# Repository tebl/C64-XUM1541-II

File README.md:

# C64 XUM1541-II
About a year ago I had a look at my collection of Commodore 64 floppies and decided that it was time, enough time had passed that even I needed to look into backing them up - hoping simply doesn't cut it in the end. I had a look at the available options, then instead of just choosing to buy something like the ZoomFloppy I wanted to build it myself. With the resources available to me [online](https://myoldcomputer.nl/commodore-64/xum1541-promicro/), all of the heavy lifting was already done. The work of transferring the designs to PCB using KiCAD resulted in the previous version, creatively called [C64 XUM1541](https://github.com/tebl/C64-XUM1541). Now that a year has gone by, mostly isolated like most of the world I wanted to make a new revision with few tweaks and so I made the  *C64 XUM1541-II*.

What had somewhat annoyed me that the [C64 XUM1541](https://github.com/tebl/C64-XUM1541) was its apparant limition when it came to running anything past version 0.7 of the [OpenCBM](https://github.com/OpenCBM/OpenCBM/tree/master/xum1541) firmware, so I finally got around to actually reading the documentation that came with it. I don't know the exact point in time the designs parted ways, but thinking practically - I instead just focused on making a version of it that would work. Mostly by adding the components required for the 7406-version of the reference design included with *OpenCBM*.

Not quite substantial enough to warrant documenting them as separate projects, I've also taken a look at implementing some of the simpler upgrades for the Commodore 1541-II as they are the type of drives I have available. Read through the included documentation before attempting to perform any of the upgrades as well as ensuring that they actually fit into the drive you have.

# 1> Modules
The following modules are available as part of this project. The additional modules are strictly not necessary as you can simply use the *C64 XUM1541-II* by itself with a drive, the parallel interface will cut the time needed to backup a single disk in half. The remaining modules mainly just affect your experience when using the drive with your physical Commodore 64, but note that most of them have been designed for use with a Commodore 1541-II disk drive.  The SpeedDOS user port adapter has been included for completeness, but before getting excited about the possiblities you should be aware that the speed gains will probably be less than what you'd obtain by simply installing [JiffyDOS](http://store.go4retro.com/categories/Commodore/Firmware/JiffyDOS/) in your [disk drive](http://store.go4retro.com/jiffydos-1541-dos-rom-overlay-image/) as well as  the [computer](http://store.go4retro.com/jiffydos-64-kernal-rom-overlay-image/) itself.

The following table lists all of the modules, click the name to get a more detailed description as well as other information for that specific module. The second and third column has been added to show which module can be used with each other, the 'XUM1541' giving a recommendation when performing backups on a modern computer. The  third column provides a recommendation when you want to use the modified drive with your physical Commodore 64.

| Module                  | C64 XUM1541-II | Physical C64 | Order  | Description |
| ----------------------- | -------------- | ------------ | ------ | ----------- |
| [C64 XUM1541-II](https://github.com/tebl/C64-XUM1541-II/tree/main/C64%20XUM1541-II) | required       | N/A     | [PCBWay](https://www.pcbway.com/project/shareproject/C64_XUM1541_II.html) | C64 XUM1541-II module for backing disks up to modern computer.
| [C64 XUM1541-II Faceplate](https://github.com/tebl/C64-XUM1541-II/tree/main/faceplates) | optional       | N/A     | [PCBWay FA1](https://www.pcbway.com/project/shareproject/C64_XUM1541_II__Faceplate_FA1_.html) | Optional faceplates suitable for installing on top of [C64 XUM1541-II](https://github.com/tebl/C64-XUM1541-II/tree/main/C64%20XUM1541-II), hiding away most of the electronics in a way that would mimic a case with a minimal amount of work.
| C64 1541-II VIA Adapter | recommended    | optional     | PCBWay | Adds a parallel interface to your Commodore 1541-II disk drive, can be used with both [C64 XUM1541-II](https://github.com/tebl/C64-XUM1541-II/tree/main/C64%20XUM1541-II) as well as physical computer with a suitable ROM upgrade.
| [C64 1541-II ROM Adapter](https://github.com/tebl/C64-XUM1541-II/tree/main/C64%201541-II%20ROM%20Adapter) | optional       | recommended  | PCBWay | Adds a switch to select between ROM images suitable for Commodore 1541-II disk drive with only a single 16KB ROM chip.
| C64 SpeedDOS Adapter    | N/A            | optional     | PCBWay | User port adapter for connecting a 1541-II disk drive with a parallel cable up to your Commodore 64, requires matching firmware on the drive as well as the computer.
| [C64 Kernal Switcher](https://github.com/tebl/C64-Kernal-Switcher) | N/A          | recommended  | [PCBWay](https://www.pcbway.com/project/shareproject/Commodore_64_Quad_Kernal_Switcher.html?inviteid=88707) | Using a custom kernal with optimizations for either serial or parallel interfaces is recommended. This board was designed for use with C64 "Longboards".

# 2> Documentation
Building an XUM1541 from scratch and getting the software ready to transfer your own physical disks, is a rather involving process. It is an afternoons worth of a project, but by following the documentation it shouldn't be a difficult task for anyone equipped with a brain for slight engineering. As the project really is just a collection of various modules that you may or may not need, I've separated the information so that the relevant documentation is included as a separate README for each of the [modules](#1-modules) - click the module name for BOM, build instructions and so forth.

When you're ready to start installing software, by first installing the firmware onto the *Arduino Pro Micro* and then installing OpenCBM, there's a separate document covering these details:
- [Firmware installation](https://github.com/tebl/C64-XUM1541-II/blob/main/documentation/firmware.md)

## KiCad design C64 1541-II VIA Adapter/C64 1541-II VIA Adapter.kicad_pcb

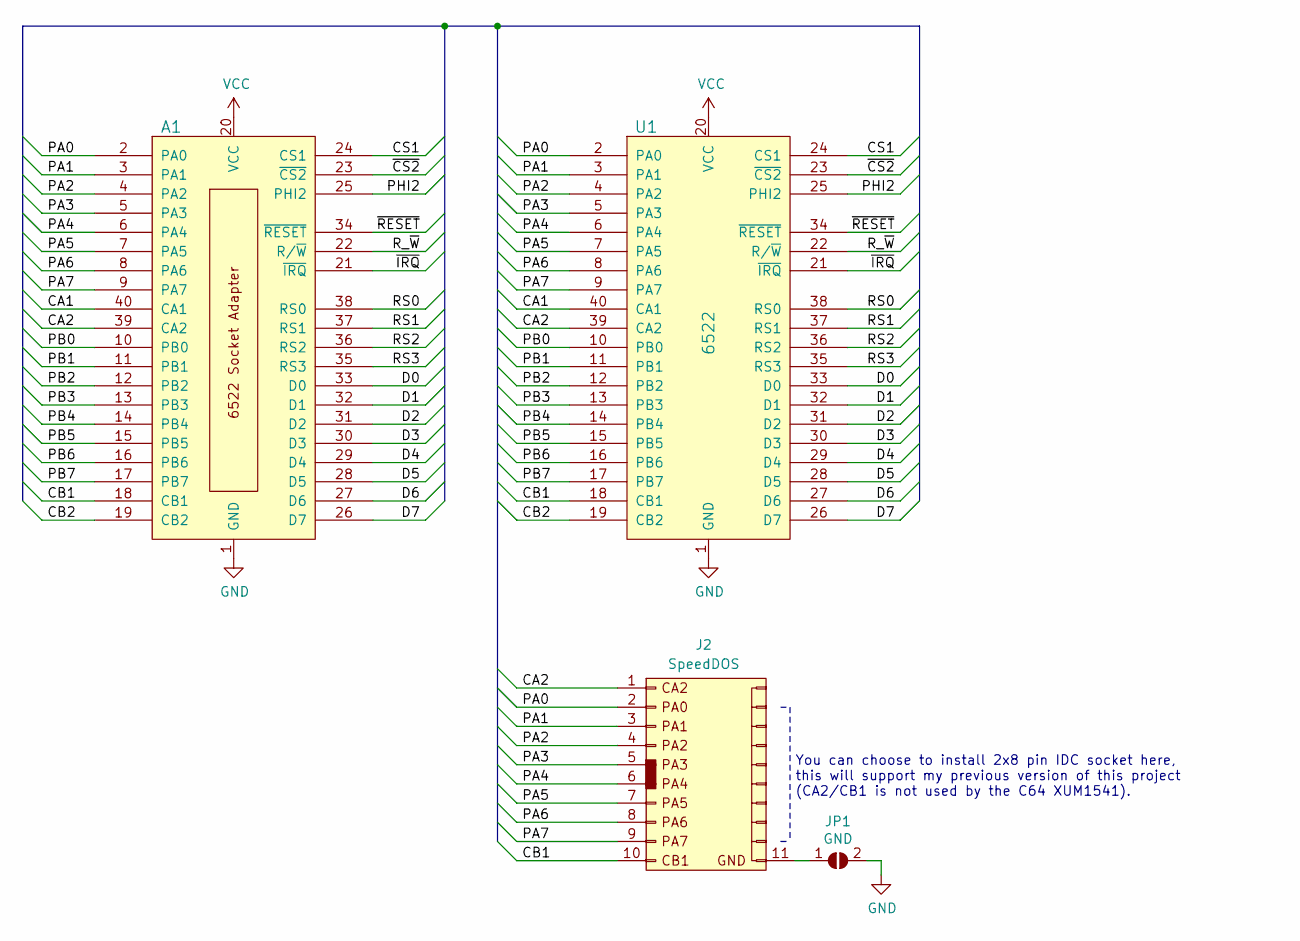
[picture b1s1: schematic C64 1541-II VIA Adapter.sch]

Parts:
A1: 6522_Adapter; DIP-40_W15.24mm_Socket
J2: SpeedDOS; SpeedDOS_IDC
JP1: GND; bridge_r
U1: 6522; DIP-40_W15.24mm_Socket

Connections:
/CA1: A1.40 (CA1), U1.40 (CA1)
/CA2: A1.39 (CA2), J2.1, U1.39 (CA2)
/CB1: A1.18 (CB1), J2.10, U1.18 (CB1)
/CB2: A1.19 (CB2), U1.19 (CB2)
/CS1: A1.24 (CS1), U1.24 (CS1)
/D0: A1.33 (D0), U1.33 (D0)
/D1: A1.32 (D1), U1.32 (D1)
/D2: A1.31 (D2), U1.31 (D2)
/D3: A1.30 (D3), U1.30 (D3)
/D4: A1.29 (D4), U1.29 (D4)
/D5: A1.28 (D5), U1.28 (D5)
/D6: A1.27 (D6), U1.27 (D6)
/D7: A1.26 (D7), U1.26 (D7)
/PA0: A1.2 (PA0), J2.2, U1.2 (PA0)
/PA1: A1.3 (PA1), J2.3, U1.3 (PA1)
/PA2: A1.4 (PA2), J2.4, U1.4 (PA2)
/PA3: A1.5 (PA3), J2.5, U1.5 (PA3)
/PA4: A1.6 (PA4), J2.6, U1.6 (PA4)
/PA5: A1.7 (PA5), J2.7 (Pin_5), U1.7 (PA5)
/PA6: A1.8 (PA6), J2.8, U1.8 (PA6)
/PA7: A1.9 (PA7), J2.9, U1.9 (PA7)
/PB0: A1.10 (PB0), U1.10 (PB0)
/PB1: A1.11 (PB1), U1.11 (PB1)
/PB2: A1.12 (PB2), U1.12 (PB2)
/PB3: A1.13 (PB3), U1.13 (PB3)
/PB4: A1.14 (PB4), U1.14 (PB4)
/PB5: A1.15 (PB5), U1.15 (PB5)
/PB6: A1.16 (PB6), U1.16 (PB6)
/PB7: A1.17 (PB7), U1.17 (PB7)
/PHI2: A1.25 (PHI2), U1.25 (PHI2)
/RS0: A1.38 (RS0), U1.38 (RS0)
/RS1: A1.37 (RS1), U1.37 (RS1)
/RS2: A1.36 (RS2), U1.36 (RS2)
/RS3: A1.35 (RS3), U1.35 (RS3)
/R_~W: A1.22 (R/~W), U1.22 (R/~W)
/~CS2: A1.23 (~CS2), U1.23 (~CS2)
/~IRQ: A1.21 (~IRQ), U1.21 (~IRQ)
/~RESET: A1.34 (~RESET), U1.34 (~RESET)
GND: A1.1 (GND), JP1.2 (B), U1.1 (GND)
unnamed: J2.11, JP1.1 (A)
VCC: A1.20 (VCC), U1.20 (VCC)

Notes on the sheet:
You can choose to install 2x8 pin IDC socket here, this will support my previous version of this project (CA2/CB1 is not used by the C64 XUM1541).

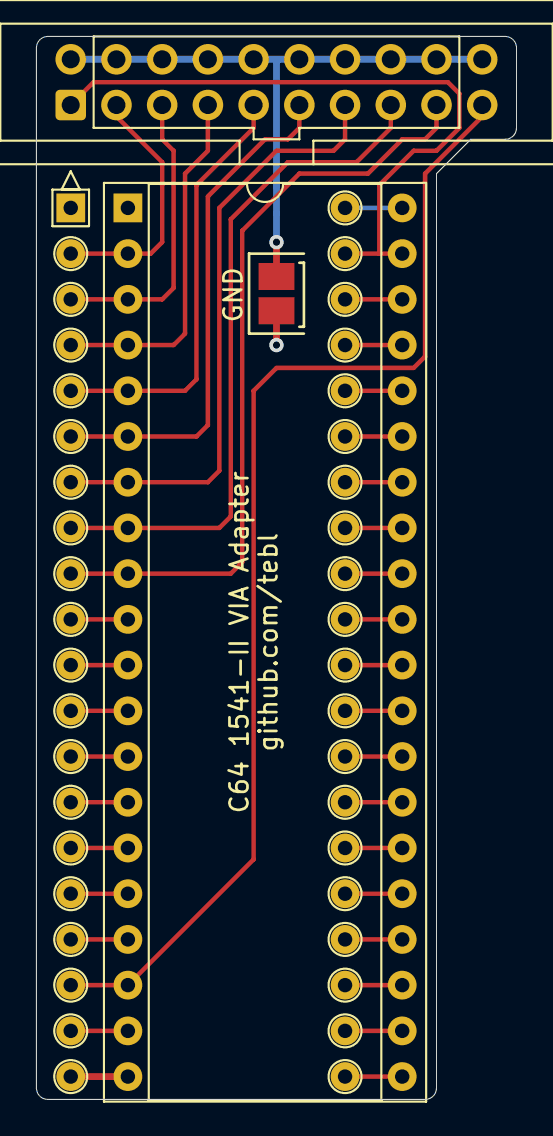
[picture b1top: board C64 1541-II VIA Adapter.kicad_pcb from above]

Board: 2 copper layers, 26.7 x 59.1 mm, 4 parts (0 on the bottom side), 41 nets.

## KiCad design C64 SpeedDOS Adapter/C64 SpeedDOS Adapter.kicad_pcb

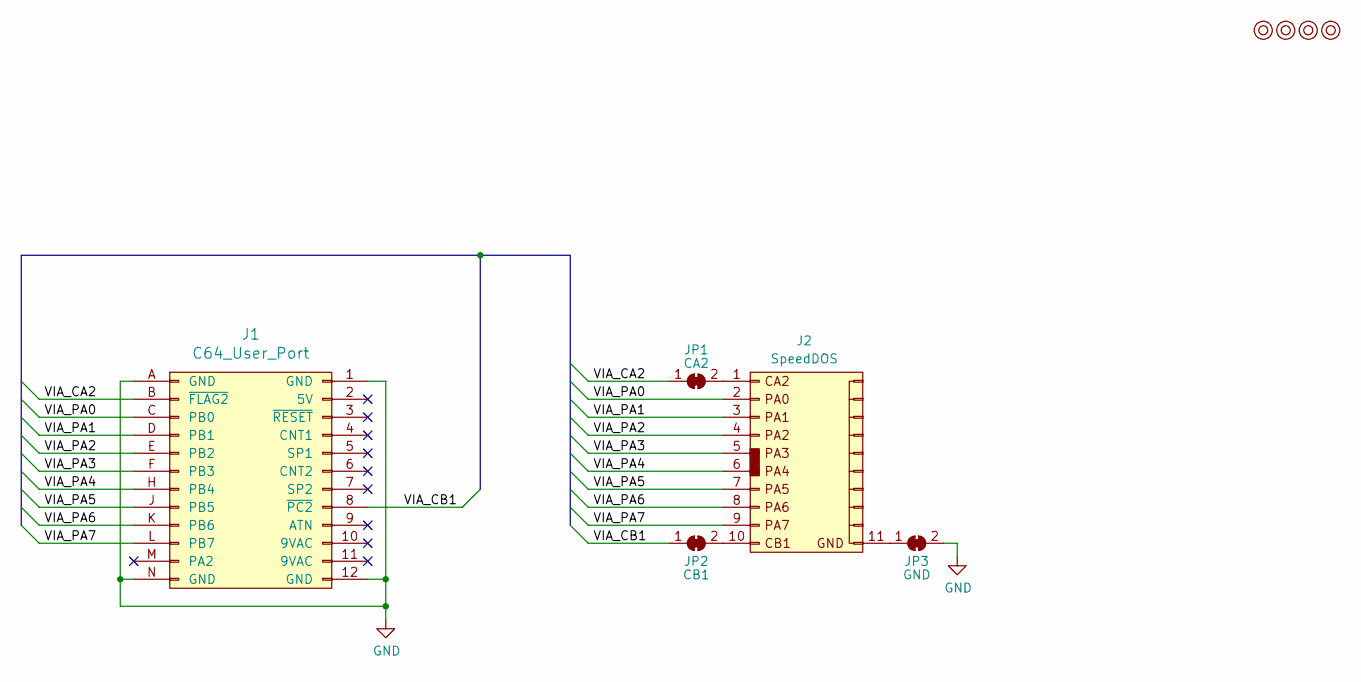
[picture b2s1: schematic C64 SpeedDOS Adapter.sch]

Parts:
J1: C64_User_Port; C64_User-Port
J2: SpeedDOS; SpeedDOS_IDC
JP1: CA2; bridge
JP2: CB1; bridge_r
JP3: GND; bridge
M1, M2, M3, M4: Mounting; M3_pin

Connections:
/VIA_CA2: J1.B (~FLAG2), JP1.1 (A)
/VIA_CB1: J1.8 (~PC2), JP2.1 (A)
/VIA_PA0: J1.C (PB0), J2.2
/VIA_PA1: J1.D (PB1), J2.3
/VIA_PA2: J1.E (PB2), J2.4
/VIA_PA3: J1.F (PB3), J2.5
/VIA_PA4: J1.H (PB4), J2.6
/VIA_PA5: J1.J (PB5), J2.7 (Pin_5)
/VIA_PA6: J1.K (PB6), J2.8
/VIA_PA7: J1.L (PB7), J2.9
GND: J1.1 (GND), J1.12 (GND), J1.A (GND), J1.N (GND), JP3.2 (B)
unnamed: J2.1, JP1.2 (B)
unnamed: J2.10, JP2.2 (B)
unnamed: J2.11, JP3.1 (A)

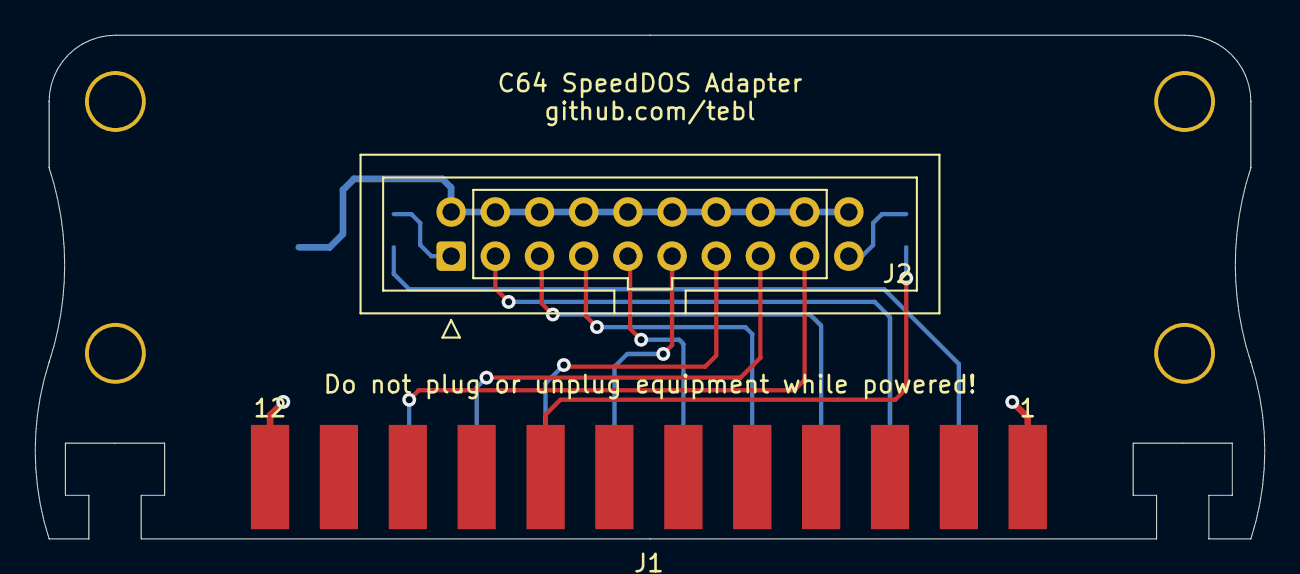
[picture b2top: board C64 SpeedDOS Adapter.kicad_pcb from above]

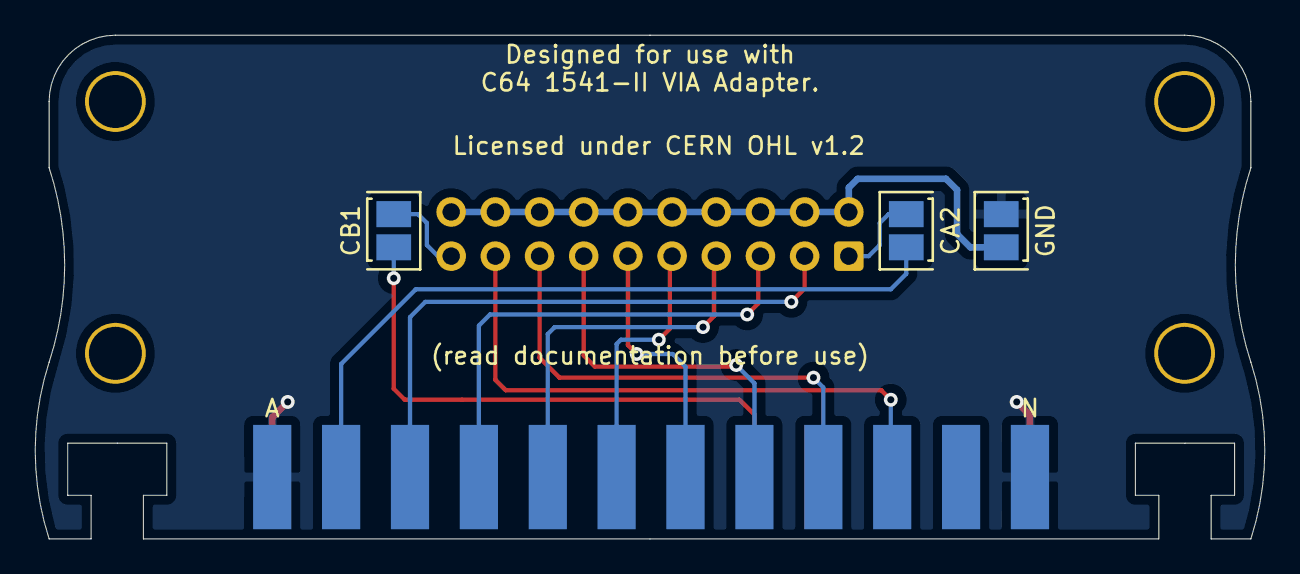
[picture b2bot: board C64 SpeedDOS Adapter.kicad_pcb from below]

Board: 2 copper layers, 70.7 x 29.0 mm, 9 parts (3 on the bottom side), 14 nets.

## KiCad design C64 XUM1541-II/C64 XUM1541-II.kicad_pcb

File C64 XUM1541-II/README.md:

# C64 XUM1541-II
If you came to this github-repository looking for the implementation of an XUM1541, then you've come to the correct place and this folder contains all of the files needed to build one for yourself. The necessary details first of course, I didn't design the original XUM1541 - the earlier heavy lifting was already done and detailed in an  article [online](https://myoldcomputer.nl/commodore-64/xum1541-promicro/). My contribution was reading it, then adapting it for easier use by designing a PCB as part of a personal project available at [C64 XUM1541](https://github.com/tebl/C64-XUM1541).

This however is an updated version from that design, mainly by integrating the 7406 inverter as described in the [OpenCBM](https://github.com/zyonee/opencbm/tree/master/xum1541) documentation. In theory this should allow the device some more durability when used together with multiple devices connected to the IEC-bus, but while I haven't had any issue with the original device - the main objective was to modify it for use with the later versions of the OpenCBM firmware (0.8). A secondary objective was to make it a more visually pleasing device from the original, which is pretty hard when dealing with a bare PCB - so I designed a separate faceplate to be installed on the top though this is a completely optional addition.

- [1> Building the C64 XUM1541-II](#1-building-the-c64-xum1541-ii)
  - [1.1> Soldering it together](#11-soldering-it-together)
  - [1.2> Assembling the unit](#12-assembling-the-unit)
  - [1.3> Testing it out](#13-testing-it-out)
- [2> Schematic](#2-schematic)
- [3> BOM](#3-bom)

# 1> Building the C64 XUM1541-II
Building the unit assumes you have at least minor experience soldering things together, recommended is at least a soldering station with adjustable temperature to get started. Commonly you'll want to start out with some 60/40 solder tin, but this'll naturally depend on availability in your area.

With the requirements when it comes to equipment sorted, now it's time to do even more shopping - head on over to the [BOM](#3-bom)-section for a somewhat specific list over components needed. Note that with sites such as ebay, AliExpress and similar sites that sell cheap chinese components, you'll need to treat these more as a suggested search term and look for something that for the most part matches the gallery pictures. I tend to use only the cheapest components available, so it should be somewhere in the top of your results.

## 1.1> Soldering it together
The construction of this unit should be straight-forward, specifically as there are only a handful of components to deal with. None of the components overlap in any way, so while there are certainly an easier route - that one would normally go from first installing the smallest components and working your way up from there. 

I suggest that you start out by studying the PCB so that you have a general overview over the components that are needed, possibly also making a mental note over the components specificly listed in the BOM as optional (component count in parenthesis). In particular, pay attention to the markings on the board for the components that need to be installed in a specific orientation (LEDs and the single IC socket).

Here we've gone ahead and installed all of the resistors, if you've bought the components as part of a kit you should note that there are two different values that you can easily pick out based on their colour bands and the number included. The IC socket have an indent on one side, this should be matched to the silkscreen on the board.

The single capacitor doesn't have a polarity so just stick it in place. The LEDs won't function when installed in the wrong orientation, ideally this should be as easy as matching the flat side to the one on the board. However there are quite a few cheaper LEDs where this isn't as easy to determine, so instead I'll just recommend that you put the shortest pin into the hole on the *flat* side. Given that you'll no doubt want a faceplate, you need to get this on the board straight - what I recommend is that you solder one of the pins, then reheat and push the component flush with the board before soldering the remaining pin.

Here we've jumped a bit ahead and finally you've found the answer to one of your original questions; why does the outline for the Arduino Pro Micro have three sets of pins on it? As you can see from the other picture added, there are a few different layouts for the Arduino Pro Micro boards - one is wider than the other! Pick the one that matches your boards before soldering pin headers onto either of the modules.

The last component that we really need to discuss is the momentary switch, mainly that it needs to be tall enough to poke through the faceplate on top. I've not found out how ebay listings measure the height of their switches, mainly because I just picked up a kit with different size switches and picked what fit. What I can tell you is that measuring just the black protruding plastic part, it needs to be around 8mm - measured from the PCB it sits around 11.5mnm above it.

Time to shut off the soldering iron. Feel the strongth welling, return to the next chapter for the exciting conclusion to this documentation. Spoiler warning: there will be a section after that one.

## 1.2> Assembling the unit
At this point we've added just about everything but the 7406, mainly just because I like dragging things out. Before doing so, I recommend spending some time to get the firmware installed onto the Arduino Pro Micro. It shouldn't matter, but it given the number of fake 7406 chips floating around it's better doing it this way. Given that installing the firmware and the accompanying OpenCBM software can be a bit more difficult than it should be, I've put together a separate [document](https://github.com/tebl/C64-XUM1541-II/blob/main/documentation/firmware.md) that should go into just about every bit of details needed to get all that set up. Return here when you're ready to move onto testing things out.

Here we've inserted the aforementioned 7406, and the device should now be ready for actual testing. Skip to the next chapter if you don't want a faceplate, because - why wouldn't you want a faceplate? They're cool.

The faceplate is just a simple PCB, the suggested way of attaching it is by using components found in cheap *M3 nylon hex* kits. It will look at its best when using an 8mm nylon hex standoff (F-F), then adding screws from both sides. If, on the other hand, you want to stay within the kit - then I suggest using the 8mm M-F standoffs, add M3 nuts on the bottom and snip off the remaining part of the nylon screw that'll poke through. Add screws on top.

## 1.3> Testing it out
When ready to test things out, we need to do some safety notifications - mainly, you can't buy any new and unused Commodore 1541 disk drives so treat them with care. They aren't plug and play like we're used to today, if you start plugging and unplugging cables while things are powered on you should probably say a prayer. Neither probably won't actually cause your vintage computer hardware to explode, but it'll happily kill your hardware in less spectacular ways. Got that? Good.

Ensure that the 1541 disk drive as well as the C64 XUM1541-II is not powered on, now connect the  IEC cable between them. Power on the disk drive, then plug the device into your modern computer. Go through the final section of my [firmware]([document](https://github.com/tebl/C64-XUM1541-II/blob/main/documentation/firmware.md)) document for some initial hints on copying your first disk, check out the software directory for a few of the batch files I personally use with the device if you just want some basic functionality without looking into all of the options (see OpenCBM documentation for that).

# 2> Schematic
The supplied KiCad files should be sufficient as both a schematic and as a  starting point for ordering PCBs (basically you could just zip the contents of the export folder and upload that on a fabrication site), the schematic is also available in [PDF-format](https://github.com/tebl/C64-XUM1541-II/tree/main/documentation/schematic) and this is what you'll need to print and work your way through this things don't work as expected after assembly.

# 3> BOM
Most parts should be easy to get a hold of from your favourite local electronic component shop, but given that I don't have access to such shops where I live so everything was based on whatever I could get cheapest from eBay/AliExpress (free shipping, but plan on waiting 3-4 weeks for delivery). 

| Reference             | Item                                                              | Count | Order  |
| --------------------- | ----------------------------------------------------------------- | ----- | ------ |
| Cartridge PCB         | Fabricate using Gerber files                                      |     1 | [PCBWay](https://www.pcbway.com/project/shareproject/C64_XUM1541_II.html)
| Faceplate PCB         | Fabricate using Gerber files                                      |    (1)| [PCBWay FA1](https://www.pcbway.com/project/shareproject/C64_XUM1541_II__Faceplate_FA1_.html)
| A1 *                  | Arduino Pro Micro                                                 |     1 |
| C1                    | 100nF ceramic capacitor (5mm pin spacing)                         |     1 |
| D1,D2                 | 5mm LED                                                           |    (2)|
| J1                    | Female S-terminal 6pin DIN PCB                                    |     1 |
| J2                    | 2x10 male IDC socket                                              |   (1) |
| R1,R4 **              | 470 ohm resistor                                                  |    (2)| 
| R2,R3,R5,R6,R7        | 100k ohm resistor                                                 |     5 | 
| SW1                   | 6x6x11mm right-angle momentary button                             |     1 |
| U1					| 7406 (DIP-14)                                                     |     1 |
| Mounting ***          | Nylon M3 hex standoffs 8mm                                        |    (4)|
| Mounting ***          | Nylon M3x6mm nylon screws                                         |    (4)|
| Mounting ***          | M3 nylon nut                                                      |    (4)|  

*) I've purchased a couple of different Arduino Pro Micro boards that had a different physical size, so take care to match up the pins to the PCB so that you solder it up to match the board you own. 

**) The value to be installed here needs to match the LEDs installed, value should be acceptable for most cheaper LEDs. If the using LEDs in any way listed as bright or are in any way clear, you'll need to calculate a suitable value in order to not blind yourself when looking at them.

***) The easiest way of ordering these is to just one of the M3 nylon standoff kits on ebay, AliExpress or any similar sites. That way you'll get more than what you need in various sizes for future projects as well.

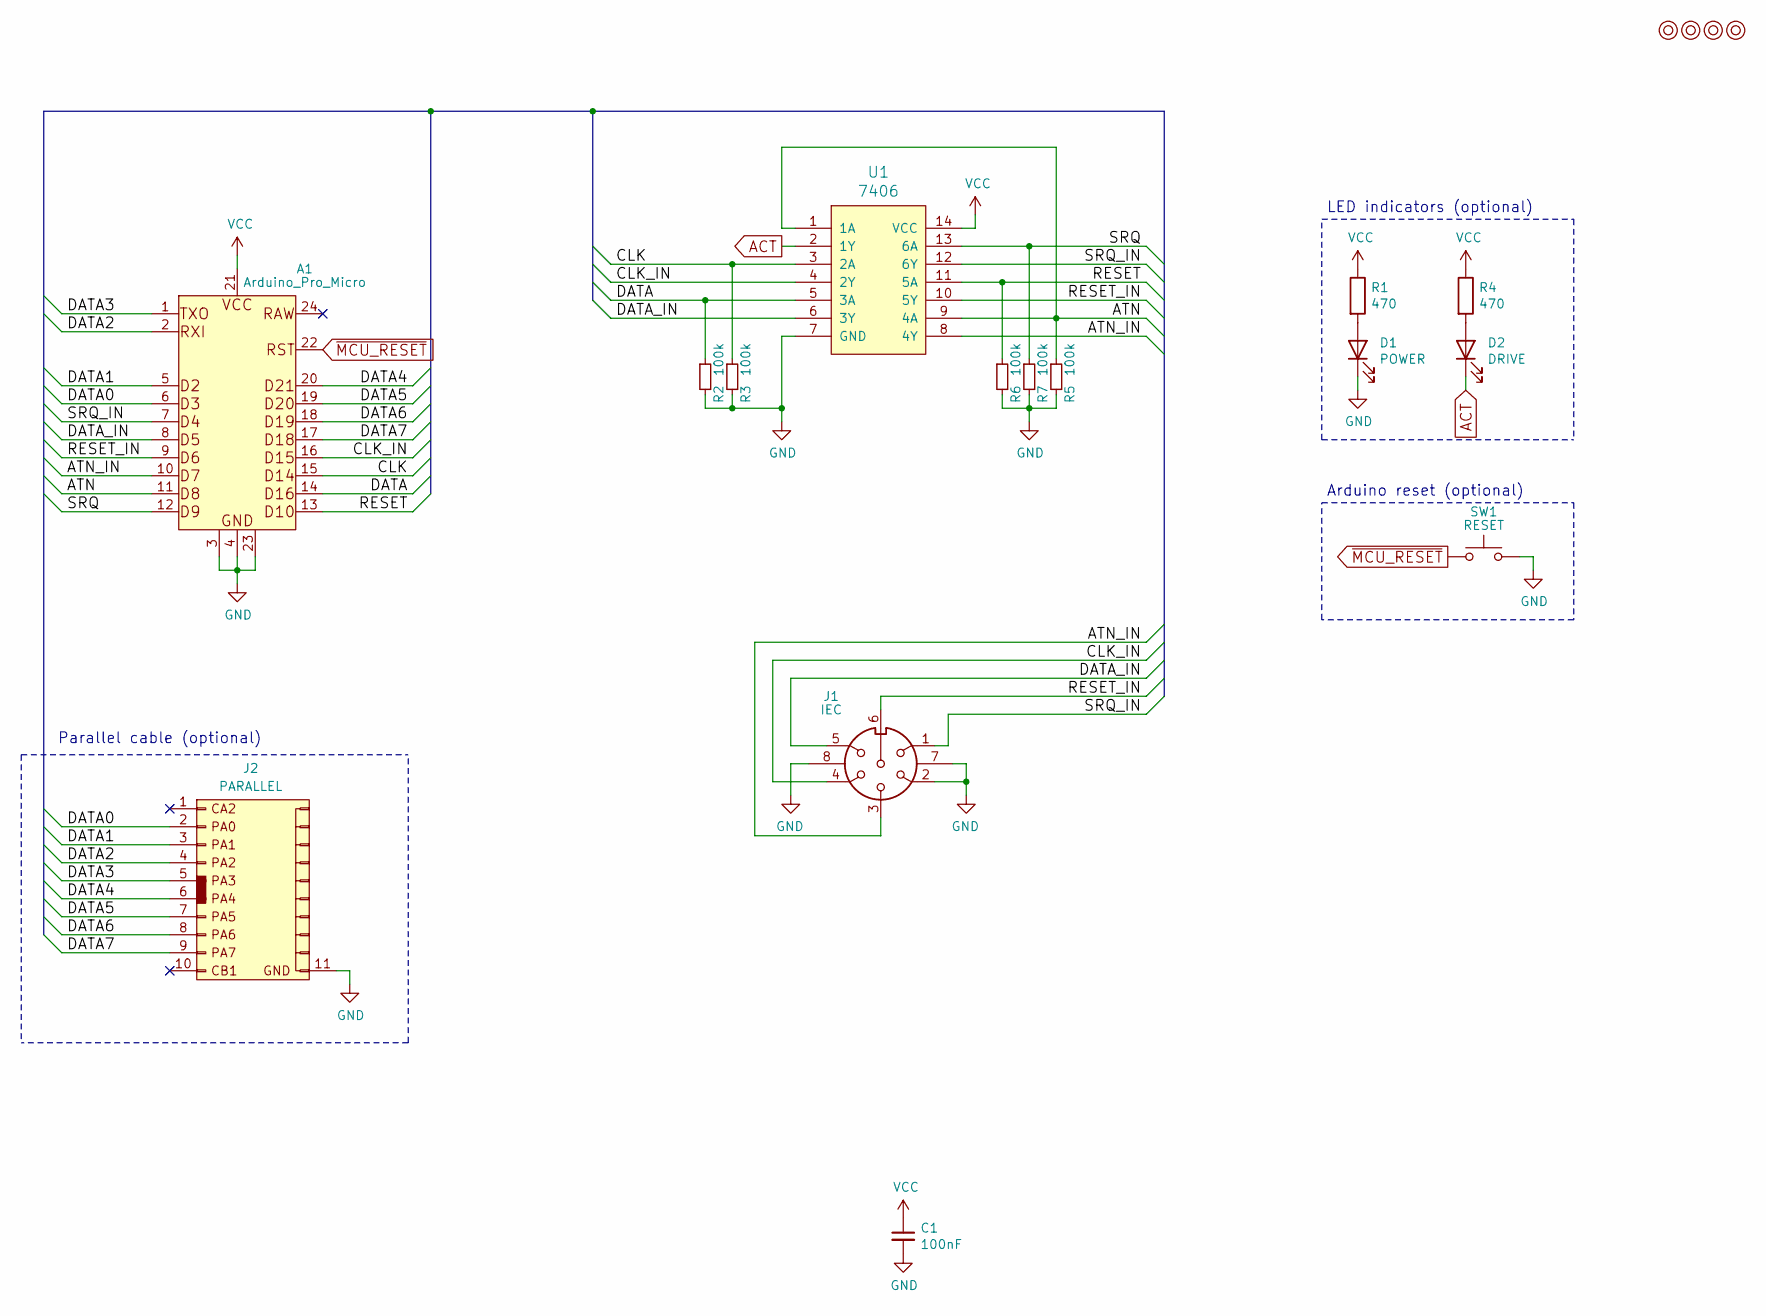
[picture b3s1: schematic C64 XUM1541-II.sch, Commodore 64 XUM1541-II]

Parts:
A1: Arduino_Pro_Micro
C1: 100nF; C_Disc_D4.7mm_W2.5mm_P5.00mm
D1: POWER; LED_D5.0mm
D2: DRIVE; LED_D5.0mm
J1: IEC; C64_IEC
J2: PARALLEL; SpeedDOS_IDC
M1, M2, M3, M4: Mounting; M3_pin
R1, R4: 470; R_Axial_DIN0207_L6.3mm_D2.5mm_P10.16mm_Horizontal
R2, R3, R5, R6, R7: 100k; R_Axial_DIN0207_L6.3mm_D2.5mm_P10.16mm_Horizontal
SW1: RESET; SW_PUSH_6mm
U1: 7406; DIP-14_W7.62mm_Socket_LongPads

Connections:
/ATN: A1.11 (D8), R5.1, U1.1 (1A), U1.9 (4A)
/ATN_IN: A1.10 (D7), J1.3, U1.8 (4Y)
/CLK: A1.15 (D14), R3.1, U1.3 (2A)
/CLK_IN: A1.16 (D15), J1.4, U1.4 (2Y)
/DATA: A1.14 (D16), R2.1, U1.5 (3A)
/DATA0: A1.6 (D3), J2.2
/DATA1: A1.5 (D2), J2.3
/DATA2: A1.2 (RXI), J2.4
/DATA3: A1.1 (TXO), J2.5
/DATA4: A1.20 (D21), J2.6
/DATA5: A1.19 (D20), J2.7 (Pin_5)
/DATA6: A1.18 (D19), J2.8
/DATA7: A1.17 (D18), J2.9
/DATA_IN: A1.8 (D5), J1.5, U1.6 (3Y)
/RESET: A1.13 (D10), R6.1, U1.11 (5A)
/RESET_IN: A1.9 (D6), J1.6, U1.10 (5Y)
/SRQ: A1.12 (D9), R7.1, U1.13 (6A)
/SRQ_IN: A1.7 (D4), J1.1, U1.12 (6Y)
ACT: D2.1 (K), U1.2 (1Y)
GND: A1.3 (GND), A1.4 (GND), A1.23 (GND), C1.2, D1.1 (K), J1.2, J1.7, J1.8, J2.11, R2.2, R3.2, R5.2, R6.2, R7.2, SW1.2, U1.7 (GND)
unnamed: D1.2 (A), R1.2
unnamed: D2.2 (A), R4.2
VCC: A1.21 (VCC), C1.1, R1.1, R4.1, U1.14 (VCC)
~MCU_RESET: A1.22 (RST), SW1.1

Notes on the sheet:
LED indicators (optional)
Parallel cable (optional)
Arduino reset (optional)

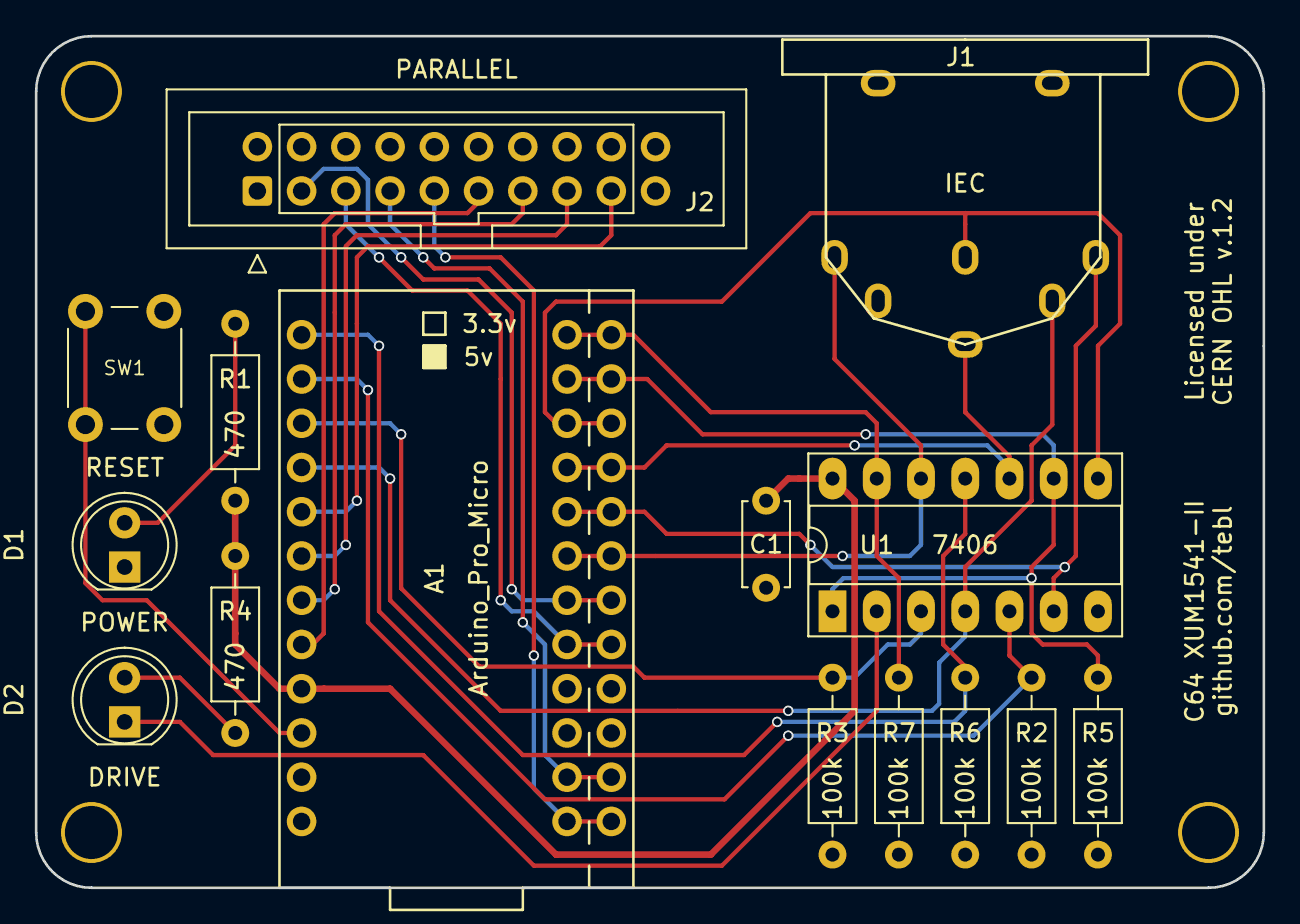
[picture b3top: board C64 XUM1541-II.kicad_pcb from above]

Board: 2 copper layers, 70.5 x 48.9 mm, 19 parts (0 on the bottom side), 24 nets.

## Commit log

2021-03-09 Updated schematic to add 7406
2021-03-09 First VIA adapter sketch
2021-03-10 User port adapter added
2021-03-10 First new layout draft
2021-03-10 Silkscreen tweaks and gerber exports
2021-03-18 Copied firmware and some batch files
2021-03-18 ACTIVITY is now DRIVE LED
2021-03-19 Updated silkscreen
2021-03-20 Increase space for M3 nut
2021-03-20 Added images
2021-04-07 Updated copy batch
2021-04-07 Tweak batch files
2021-04-07 Moved connector to clear stepper motor
2021-04-07 Rotated parallel connector
2021-04-08 Updated gerber files and small tweaks
2021-04-08 Added some images
2021-04-08 Better preview
2021-04-08 Added schematic
2021-04-08 Shorten ROM board a little bit
2021-04-08 Changed preview
2021-04-08 Schematic notes added
2021-04-08 firmware images
2021-04-08 Blank README
2021-04-08 Added image
2021-04-08 Renamed some files
2021-04-09 Added firmware installation document
2021-04-09 Added note about device
2021-04-09 typo
2021-04-27 Updated firmware install pictures
2021-04-27 Resistor note
2021-04-27 Build images
2021-04-29 Added GND jumper to adapter
2021-04-29 Missing files
2021-04-29 Ignore test files
2021-04-29 Link remaining pins
2021-04-29 Added GND jumper
2021-04-29 Gerber export
2021-05-07 Arduino boards
2021-05-08 README content
2021-05-19 Added faceplate
2021-06-28 Added module README
2021-08-02 Added some documentation
2022-01-25 Alternative faceplate
2022-01-25 Remove temporary files
2022-02-18 Add images
2022-02-18 Tweak documentation

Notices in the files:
C64 1541-II VIA Adapter/C64 1541-II VIA Adapter.kicad_pcb:
Licensed under CERN OHL v1.2
C64 XUM1541-II/C64 XUM1541-II.kicad_pcb:
CERN OHL v.1.2
